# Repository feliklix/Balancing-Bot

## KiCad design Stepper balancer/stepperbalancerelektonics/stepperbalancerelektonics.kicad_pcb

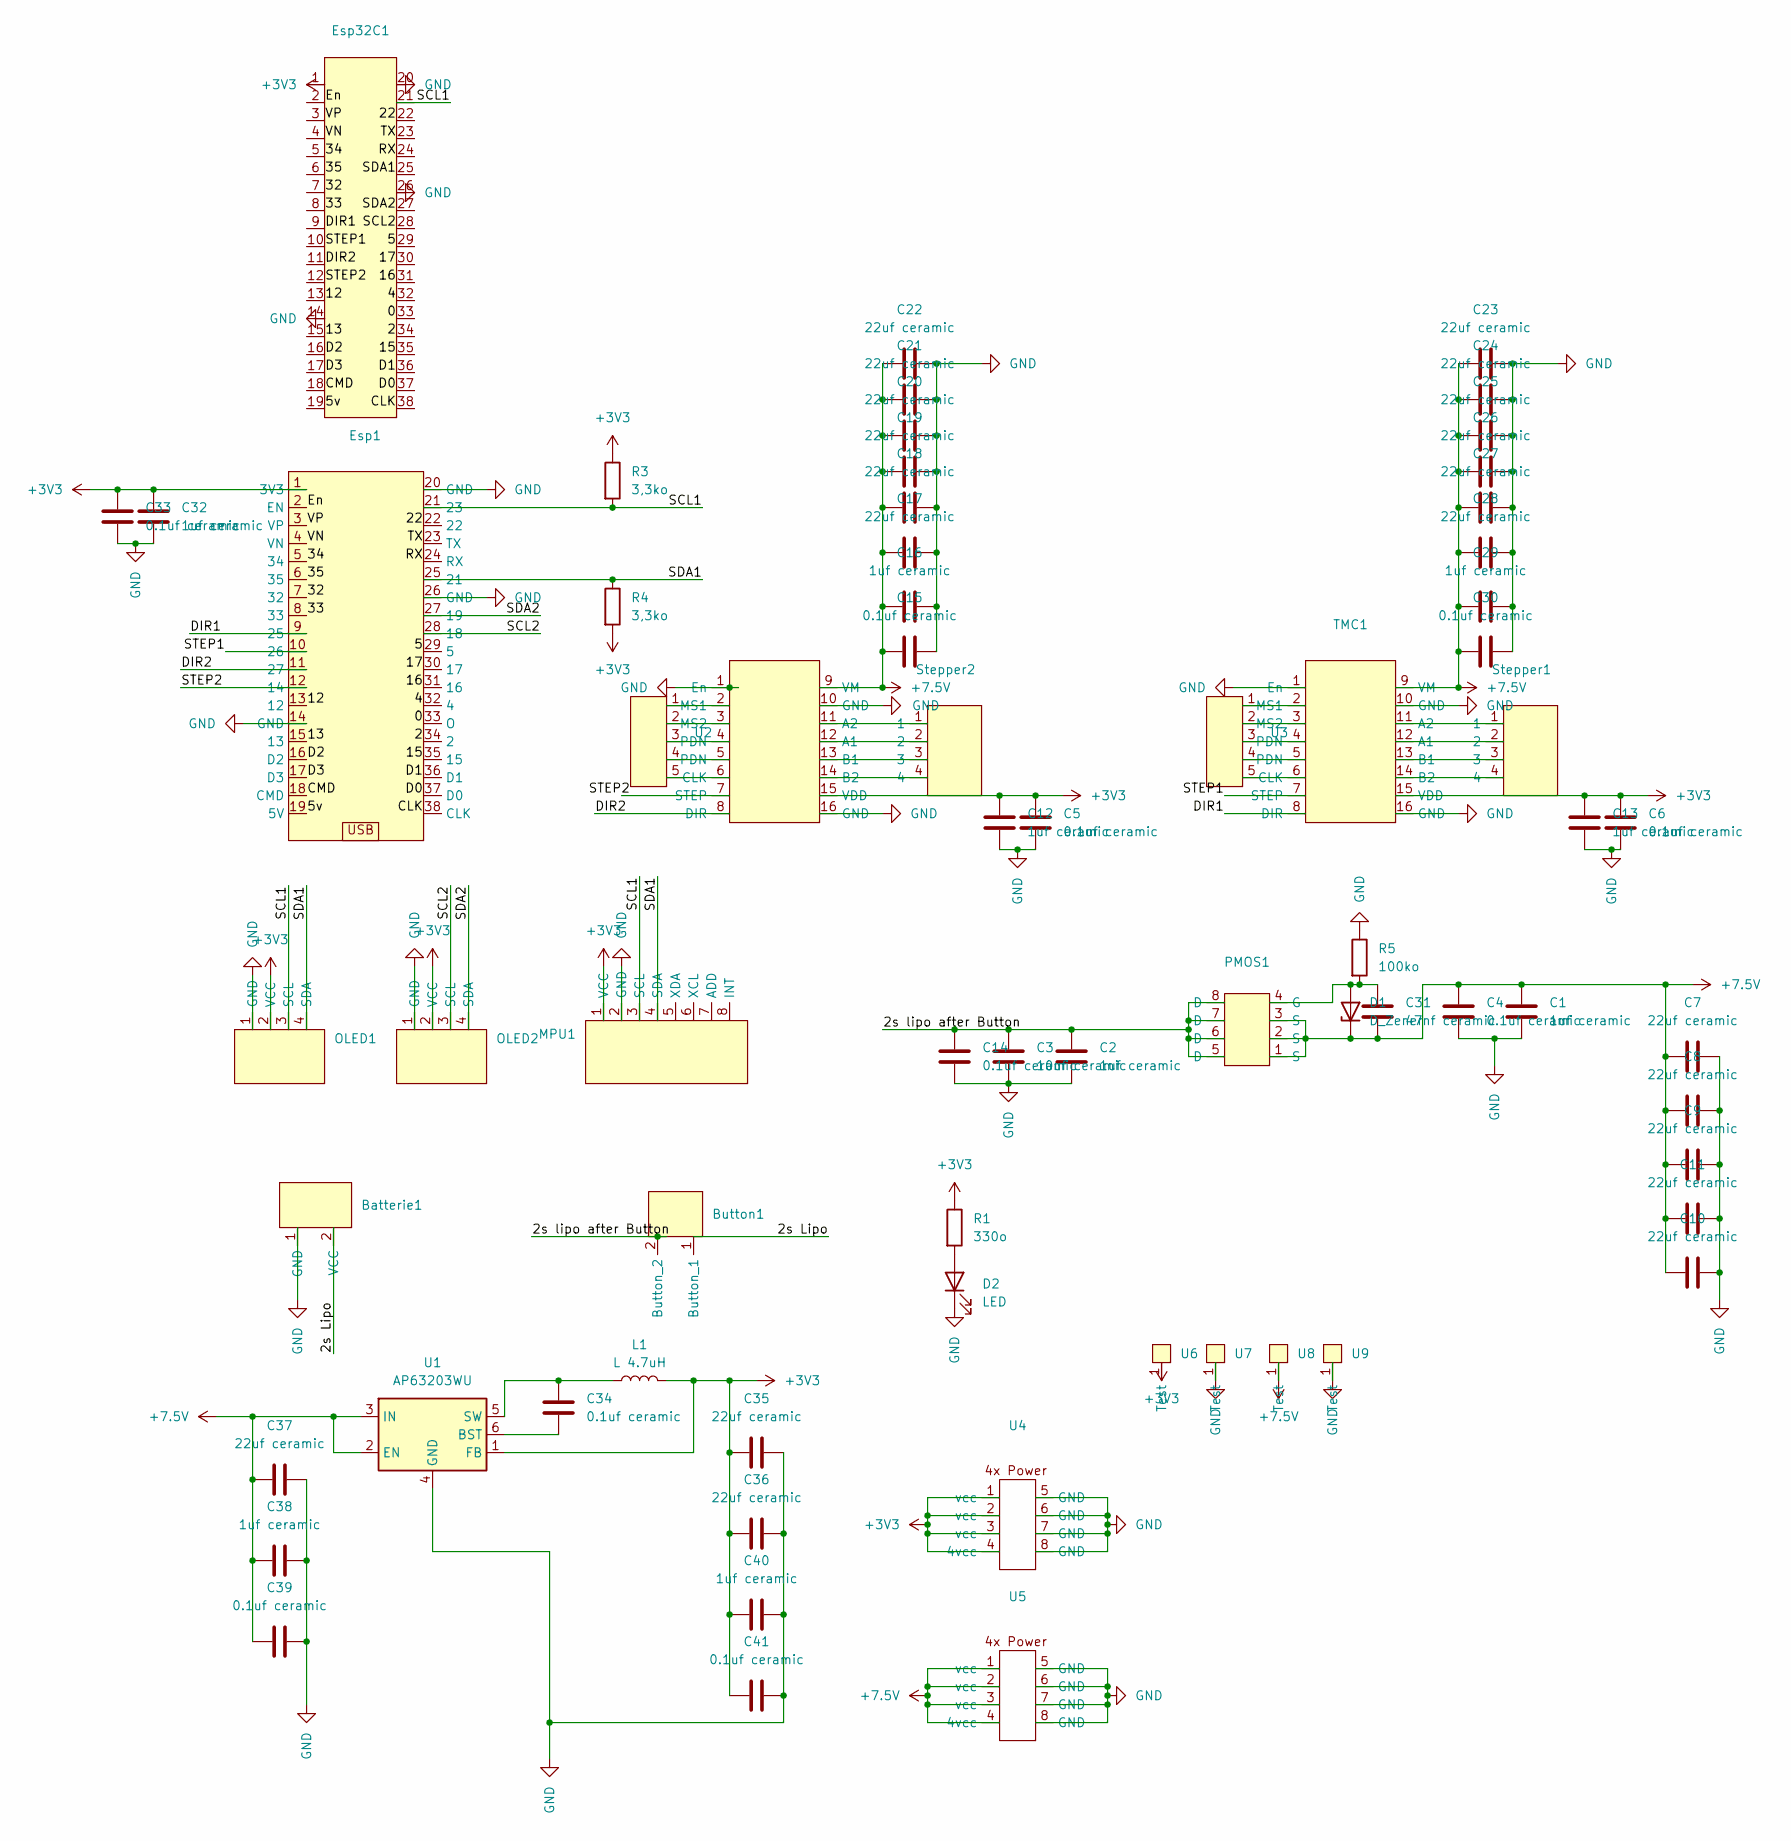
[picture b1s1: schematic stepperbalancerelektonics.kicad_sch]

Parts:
Batterie1: Batterie
Button1: Button_connector
C1, C2, C12, C13, C16, C29, C32, C38, C40: 1uf ceramic; C_0805_2012Metric; LCSC C28323
C3: 10uf ceramic; C_0805_2012Metric; LCSC C33546007
C4, C5, C6, C14, C15, C30, C33, C34, C39, C41: 0.1uf ceramic; C_0805_2012Metric; LCSC C476766
C7, C8, C9, C10, C11, C17, C18, C19, C20, C21, C22, C23, C24, C25, C26, C27, C28, C35, C36, C37: 22uf ceramic; C_0805_2012Metric; LCSC C602037
C31: 47nf ceramic; C_0805_2012Metric; LCSC C1745
D1: D_Zener; D_SOD-123; LCSC C21570
D2: LED; LED_0805_2012Metric; LCSC C19273154
Esp1: ESP32
Esp32C1: ESP breakouts
L1: L 4.7uH; L_Chilisin_BMRB00060624; LCSC C41415576
MPU1: MPU6050
OLED1, OLED2: OLED
PMOS1: SOIC-8_5.3x5.3mm_P1.27mm; LCSC C146318
R1: 330o; R_0805_2012Metric; LCSC C17630
R3, R4: 3,3ko; R_0805_2012Metric; LCSC C2907250
R5: 100ko; R_0805_2012Metric; LCSC C96346
Stepper1, Stepper2: Stepper
TMC1, TMC2: TMC2209
U1: AP63203WU; TSOT-23-6; LCSC C780769
U2, U3: Stepper extra connecter
U4, U5: 4x Power
U6, U7, U8, U9: Test Pad

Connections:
+3V3: C5.1, C6.1, C12.2, C13.2, C32.2, C33.1, C35.1, C36.1, C40.2, C41.1, Esp1.1 (3V3), Esp32C1.1, L1.2, MPU1.1 (VCC), OLED1.2 (VCC), OLED2.2 (VCC), R1.1, R3.1, R4.2, TMC1.15 (VDD), TMC2.15 (VDD), U1.1 (FB), U4.1 (vcc), U4.2 (vcc), U4.3 (vcc), U4.4 (4vcc), U6.1 (Test)
+7.5V: C1.1, C4.1, C7.1, C8.1, C9.1, C10.1, C11.1, C15.1, C16.2, C17.1, C18.1, C19.1, C20.1, C21.1, C22.1, C23.1, C24.1, C25.1, C26.1, C27.1, C28.1, C29.2, C30.1, C31.1, C37.2, C38.2, C39.1, D1.1 (K), PMOS1.1 (S), PMOS1.2 (S), PMOS1.3 (S), TMC1.9 (VM), TMC2.9 (VM), U1.2 (EN), U1.3 (IN), U5.1 (vcc), U5.2 (vcc), U5.3 (vcc), U5.4 (4vcc), U8.1 (Test)
/0: Esp1.33 (O), Esp32C1.33
/2: Esp1.34 (2), Esp32C1.34
/2s Lipo: Batterie1.2 (VCC), Button1.1 (Button)
/2s lipo after Button: Button1.2 (Button), C2.2, C3.1, C14.1, PMOS1.5 (D), PMOS1.6 (D), PMOS1.7 (D), PMOS1.8 (D)
/4: Esp1.32 (4), Esp32C1.32
/5: Esp1.29 (5), Esp32C1.29
/5v: Esp1.19 (5V), Esp32C1.19
/12: Esp1.13 (12), Esp32C1.13
/13: Esp1.15 (13), Esp32C1.15
/15: Esp1.35 (15), Esp32C1.35
/16: Esp1.31 (16), Esp32C1.31
/17: Esp1.30 (17), Esp32C1.30
/22: Esp1.22, Esp32C1.22
/32: Esp1.7 (32), Esp32C1.7
/33: Esp1.8 (33), Esp32C1.8
/34: Esp1.5 (34), Esp32C1.5
/35: Esp1.6 (35), Esp32C1.6
/CLK: Esp1.38 (CLK), Esp32C1.38
/CMD: Esp1.18 (CMD), Esp32C1.18
/D0: Esp1.37 (D0), Esp32C1.37
/D1: Esp1.36 (D1), Esp32C1.36
/D2: Esp1.16 (D2), Esp32C1.16
/D3: Esp1.17 (D3), Esp32C1.17
/DIR1: Esp1.9 (25), Esp32C1.9, TMC1.8 (DIR)
/DIR2: Esp1.11 (27), Esp32C1.11, TMC2.8 (DIR)
/En: Esp1.2 (EN), Esp32C1.2
/RX: Esp1.24 (RX), Esp32C1.24
/SCL1: Esp1.21 (23), Esp32C1.21, MPU1.3 (SCL), OLED1.3 (SCL), R3.2
/SCL2: Esp1.28 (18), Esp32C1.28, OLED2.3 (SCL)
/SDA1: Esp1.25 (21), Esp32C1.25, MPU1.4 (SDA), OLED1.4 (SDA), R4.1
/SDA2: Esp1.27 (19), Esp32C1.27, OLED2.4 (SDA)
/STEP1: Esp1.10 (26), Esp32C1.10, TMC1.7 (STEP)
/STEP2: Esp1.12 (14), Esp32C1.12, TMC2.7 (STEP)
/TX: Esp1.23 (TX), Esp32C1.23
/VN: Esp1.4 (VN), Esp32C1.4
/VP: Esp1.3 (VP), Esp32C1.3
GND: Batterie1.1 (GND), C1.2, C2.1, C3.2, C4.2, C5.2, C6.2, C7.2, C8.2, C9.2, C10.2, C11.2, C12.1, C13.1, C14.2, C15.2, C16.1, C17.2, C18.2, C19.2, C20.2, C21.2, C22.2, C23.2, C24.2, C25.2, C26.2, C27.2, C28.2, C29.1, C30.2, C32.1, C33.2, C35.2, C36.2, C37.1, C38.1, C39.2, C40.1, C41.2, D2.1 (K), Esp1.14 (GND), Esp1.20 (GND), Esp1.26 (GND), Esp32C1.14, Esp32C1.20, Esp32C1.26, MPU1.2 (GND), OLED1.1 (GND), OLED2.1 (GND), R5.1, TMC1.1 (En), TMC1.10 (GND), TMC1.16 (GND), TMC2.1 (En), TMC2.10 (GND), TMC2.16 (GND), U1.4 (GND), U4.5 (GND), U4.6 (GND), U4.7 (GND), U4.8 (GND), U5.5 (GND), U5.6 (GND), U5.7 (GND), U5.8 (GND), U7.1 (Test), U9.1 (Test)
unnamed: C31.2, D1.2 (A), PMOS1.4 (G), R5.2
unnamed: D2.2 (A), R1.2
unnamed: Stepper1.2, TMC1.12 (A1)
unnamed: Stepper1.1, TMC1.11 (A2)
unnamed: Stepper1.3, TMC1.13 (B1)
unnamed: Stepper1.4, TMC1.14 (B2)
unnamed: TMC1.6 (CLK), U3.5
unnamed: TMC1.2 (MS1), U3.1
unnamed: TMC1.3 (MS2), U3.2
unnamed: TMC1.4 (PDN), U3.3
unnamed: TMC1.5 (PDN), U3.4
unnamed: Stepper2.2, TMC2.12 (A1)
unnamed: Stepper2.1, TMC2.11 (A2)
unnamed: Stepper2.3, TMC2.13 (B1)
unnamed: Stepper2.4, TMC2.14 (B2)
unnamed: TMC2.6 (CLK), U2.5
unnamed: TMC2.2 (MS1), U2.1
unnamed: TMC2.3 (MS2), U2.2
unnamed: TMC2.4 (PDN), U2.3
unnamed: TMC2.5 (PDN), U2.4
unnamed: C34.2, U1.6 (BST)
unnamed: C34.1, L1.1, U1.5 (SW)

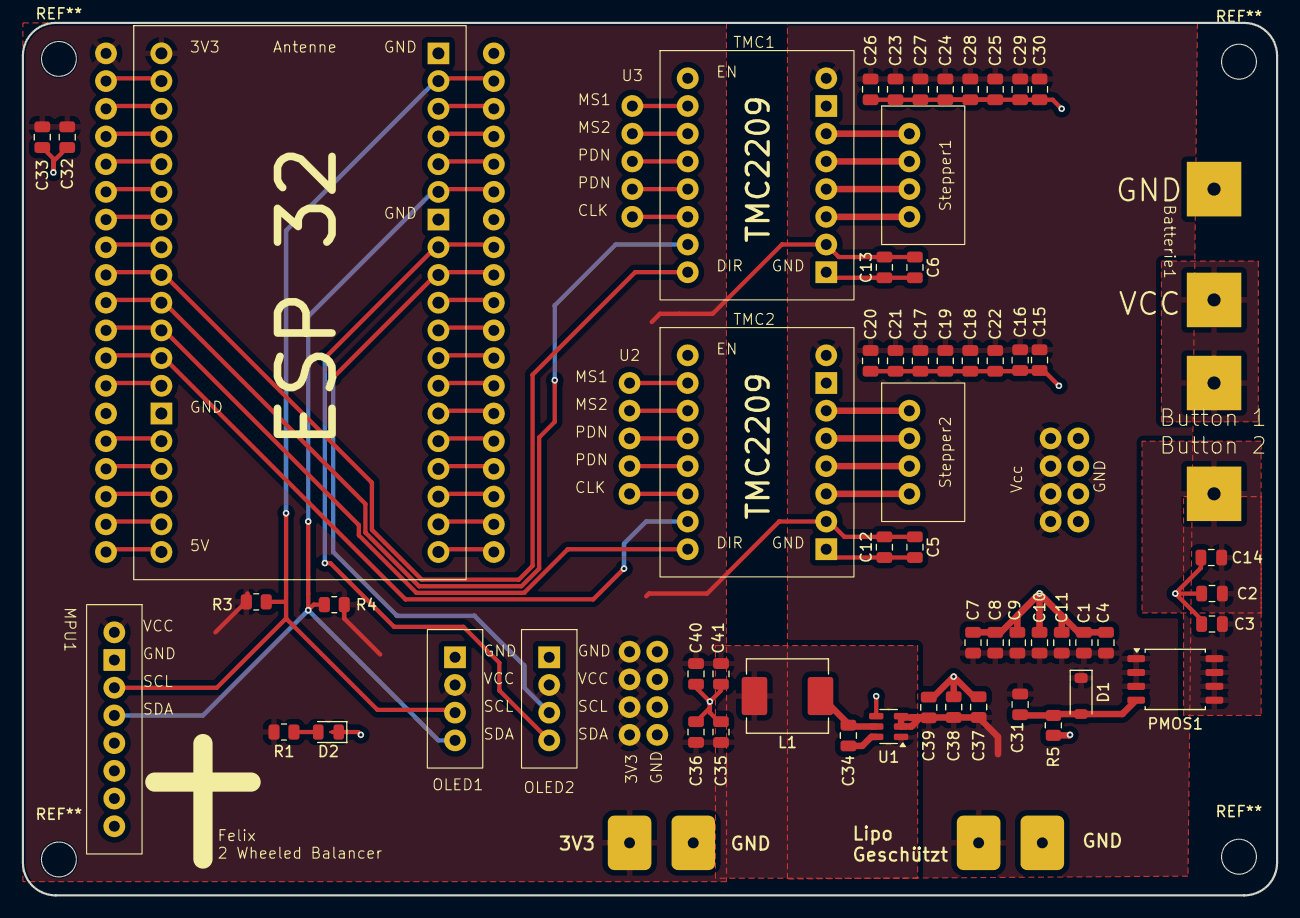
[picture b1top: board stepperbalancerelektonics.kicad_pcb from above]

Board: 2 copper layers, 115.0 x 80.0 mm, 69 parts (0 on the bottom side), 61 nets.

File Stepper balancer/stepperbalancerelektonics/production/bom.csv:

Designator,Footprint,Quantity,Value,LCSC Part #
"C1, C12, C13, C16, C2, C29, C32, C38, C40",0805,9,1uf ceramic,C28323
"C10, C11, C17, C18, C19, C20, C21, C22, C23, C24, C25, C26, C27, C28, C35, C36, C37, C7, C8, C9",0805,20,22uf ceramic,C602037
"C14, C15, C30, C33, C34, C39, C4, C41, C5, C6",0805,10,0.1uf ceramic,C476766
C3,0805,1,10uf ceramic,C33546007
C31,0805,1,47nf ceramic,C1745
D1,D_SOD-123,1,D_Zener,C21570
D2,0805,1,LED,C19273154
L1,L_Chilisin_BMRB00060624,1,L 4.7uH,C41415576
PMOS1,SOIC-8_5.3x5.3mm_P1.27mm,1,~,C146318
R1,0805,1,330o,C17630
"R3, R4",0805,2,"3,3ko",C2907250
R5,0805,1,100ko,C96346
U1,TSOT-23-6,1,AP63203WU,C780769

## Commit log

2025-10-17 pcb files
